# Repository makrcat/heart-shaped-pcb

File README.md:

## Heart Shaped PCB
perhaps it will be a bike light
made using KiCAD.

## FOR SPICE MAKE SURE TO

or else it will be stupid and not run

## Images

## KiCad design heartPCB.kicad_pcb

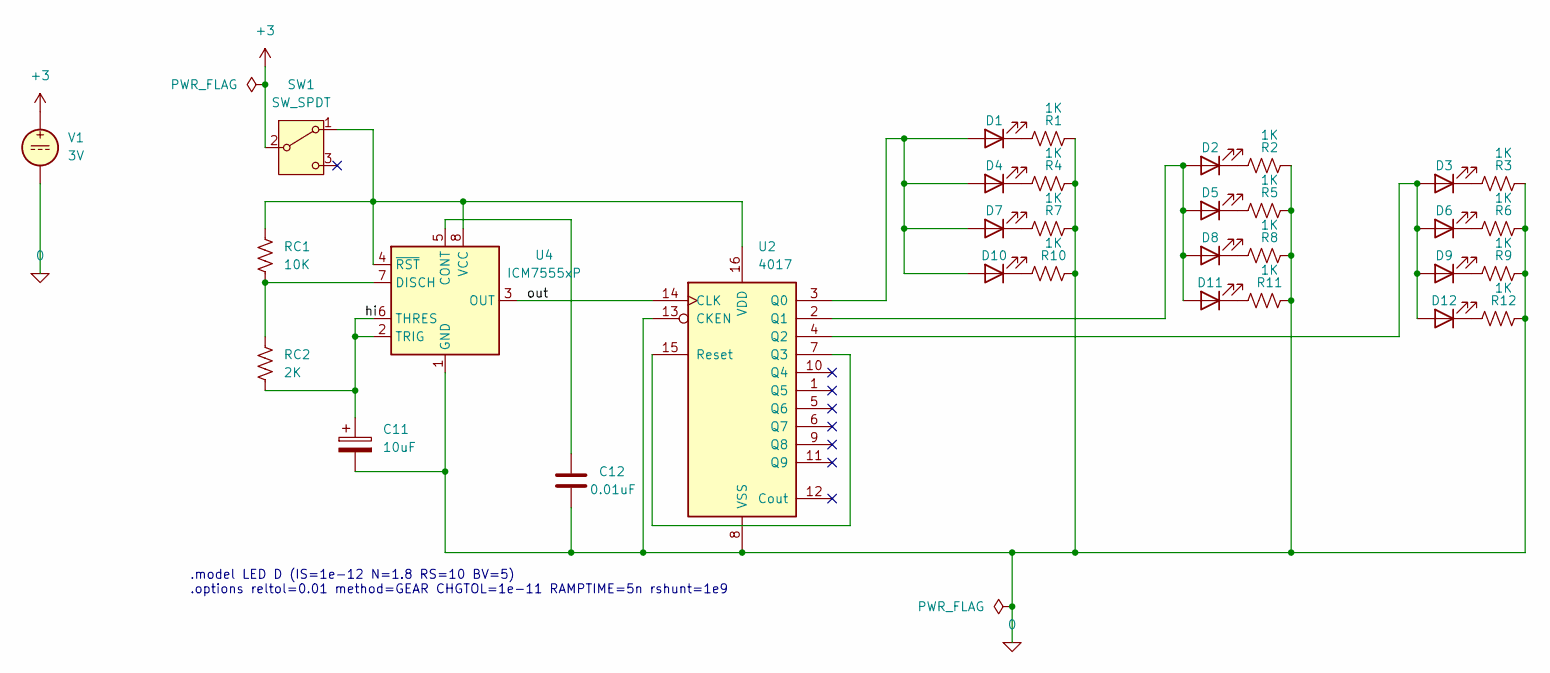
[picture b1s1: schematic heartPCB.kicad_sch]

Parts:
C11: 10uF; CP_Radial_D5.0mm_P2.00mm
C12: 0.01uF; C_Disc_D5.0mm_W2.5mm_P2.50mm
D1, D2, D3, D4, D5, D6, D7, D8, D9, D10, D11, D12: LED; LED_D5.0mm
R1, R2, R3, R4, R5, R6, R7, R8, R9, R10, R11, R12: 1K; R_Axial_DIN0207_L6.3mm_D2.5mm_P7.62mm_Horizontal
RC1: 10K; R_Axial_DIN0207_L6.3mm_D2.5mm_P7.62mm_Horizontal
RC2: 2K; R_Axial_DIN0207_L6.3mm_D2.5mm_P7.62mm_Horizontal
SW1: SW_SPDT; SW_Slide-03_Wuerth-WS-SLTV_10x2.5x6.4_P2.54mm
U2: 4017; DIP-16_W7.62mm_LongPads
U4: ICM7555xP; DIP-8_W7.62mm_LongPads
V1: 3V; BatteryHolder_Keystone_3034_1x20mm

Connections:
0: C11.2, C12.2, R1.2, R2.2, R3.2, R4.2, R5.2, R6.2, R7.2, R8.2, R9.2, R10.2, R11.2, R12.2, U2.8 (VSS), U2.13 (CKEN), U4.1 (GND), V1.2
+3: SW1.2 (B), V1.1
/hi: C11.1, RC2.2, U4.2 (TRIG), U4.6 (THRES)
/out: U2.14 (CLK), U4.3 (OUT)
unnamed: D1.2 (A), D4.2 (A), D7.2 (A), D10.2 (A), U2.3 (Q0)
unnamed: D1.1 (K), R1.1
unnamed: D2.1 (K), R2.1
unnamed: D3.1 (K), R3.1
unnamed: D4.1 (K), R4.1
unnamed: D5.1 (K), R5.1
unnamed: D6.1 (K), R6.1
unnamed: D7.1 (K), R7.1
unnamed: D8.1 (K), R8.1
unnamed: D9.1 (K), R9.1
unnamed: D10.1 (K), R10.1
unnamed: D2.2 (A), D5.2 (A), D8.2 (A), D11.2 (A), U2.2 (Q1)
unnamed: D11.1 (K), R11.1
unnamed: D3.2 (A), D6.2 (A), D9.2 (A), D12.2 (A), U2.4 (Q2)
unnamed: D12.1 (K), R12.1
unnamed: RC1.1, SW1.1 (A), U2.16 (VDD), U4.4 (~RST), U4.8 (VCC)
unnamed: U2.7 (Q3), U2.15 (Reset)
unnamed: C12.1, U4.5 (CONT)
unnamed: RC1.2, RC2.1, U4.7 (DISCH)

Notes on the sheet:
.model LED D (IS=1e-12 N=1.8 RS=10 BV=5) .options reltol=0.01 method=GEAR CHGTOL=1e-11 RAMPTIME=5n rshunt=1e9

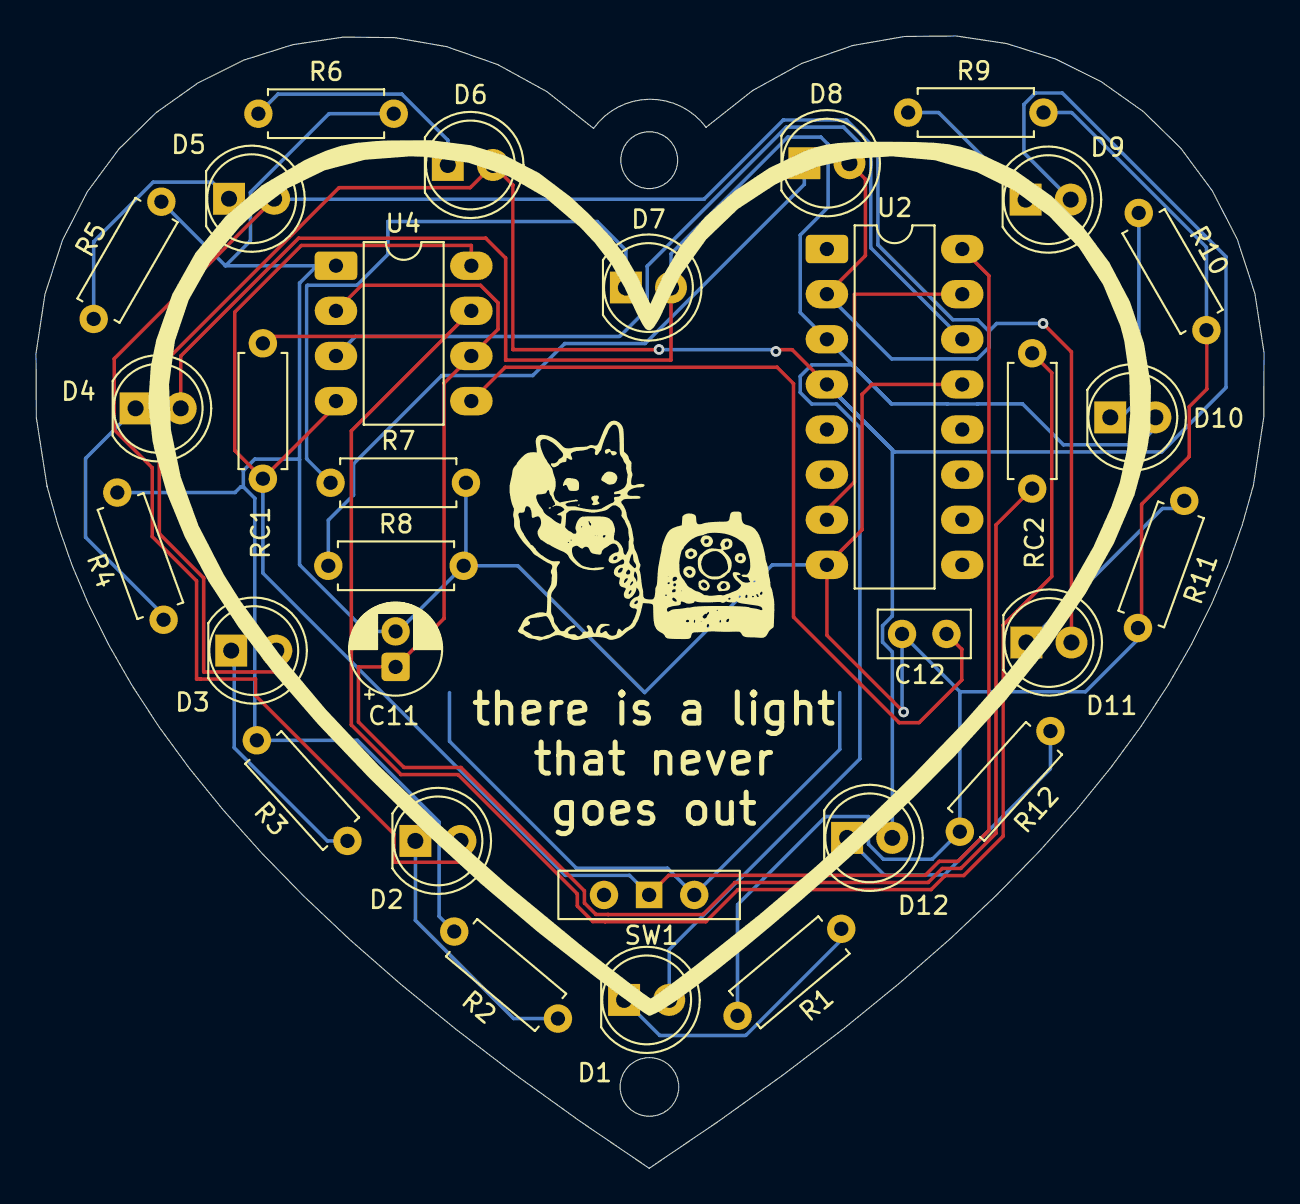
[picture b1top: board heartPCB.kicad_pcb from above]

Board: 2 copper layers, 69.1 x 63.7 mm, 32 parts (1 on the bottom side), 23 nets.

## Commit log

2026-03-18 # This is a combination of 2 commits. # This is the 1st commit message:
    readme file
    # This is the commit message #2:
    oops file path change
2026-03-18 schematic footprint changes
2026-03-18 readme update
